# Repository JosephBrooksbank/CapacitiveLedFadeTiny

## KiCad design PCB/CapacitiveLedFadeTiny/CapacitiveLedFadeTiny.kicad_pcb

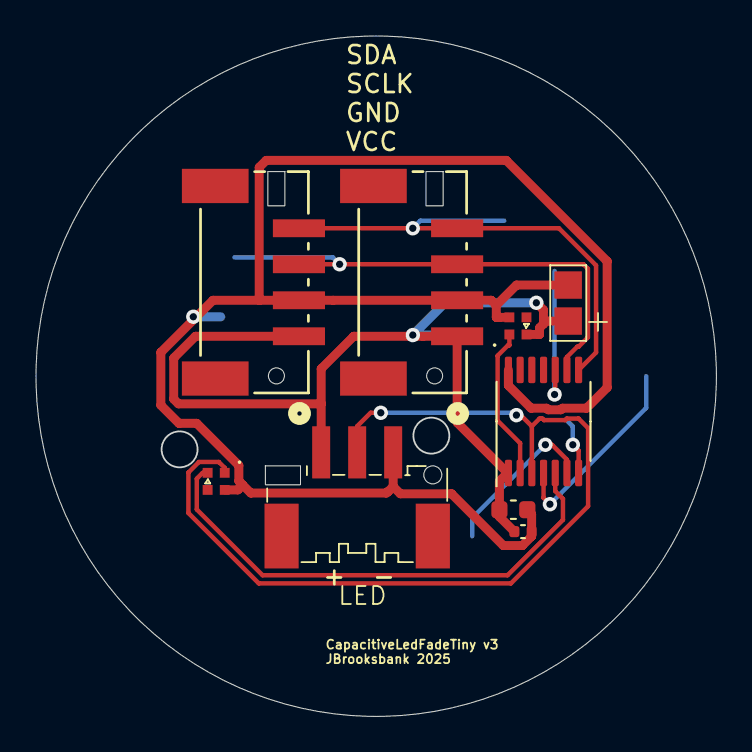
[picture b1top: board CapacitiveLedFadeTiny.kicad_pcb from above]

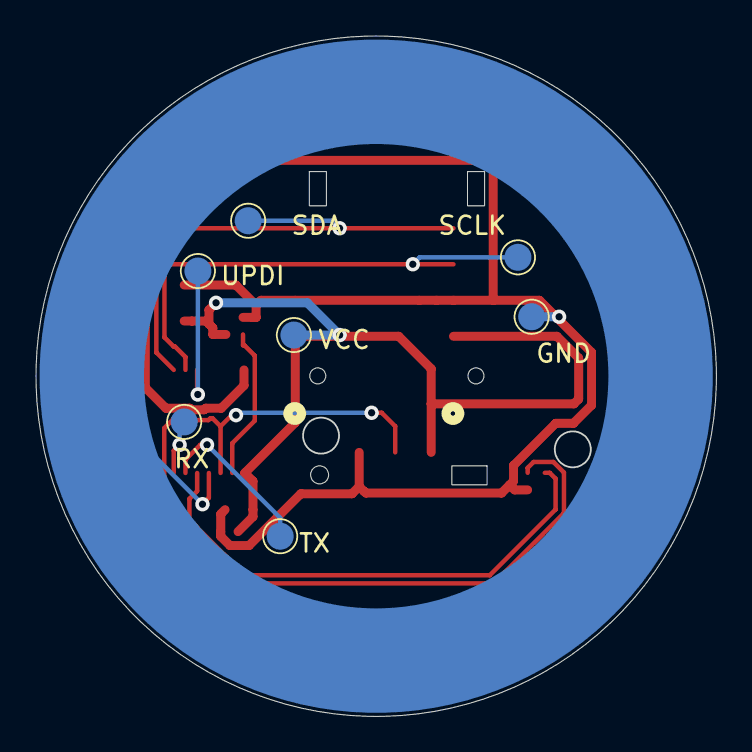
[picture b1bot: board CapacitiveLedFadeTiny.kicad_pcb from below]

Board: 2 copper layers, 37.7 x 37.7 mm, 17 parts (7 on the bottom side), 11 nets.

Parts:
BusIn1: Bus In; CONN_BM04B-PASS-1-TFTLFSN_JST
BusOut1: Bus Out; CONN_BM04B-PASS-1-TFTLFSN_JST
C3: 0.1uf; C_0402_1005Metric
C4: 1uf; C_0603_1608Metric
GND: GND; TestPoint_Pad_1.5mm_circular
J1: Antenna; CapacitiveAntenna
J6: Power Inject; 2Pad
LED: LEDs; BM03B-PASS-1-TFT
LED1, LED2: SK6805-EC15
RX: PadRX; TestPoint_Pad_1.5mm_circular
SCLK: SCLK; TestPoint_Pad_1.5mm_circular
SDA: SDA; TestPoint_Pad_1.5mm_circular
TX: PadTX; TestPoint_Pad_1.5mm_circular
U1: ATtiny3224-X; TSSOP-14_4.4x5mm_P0.65mm
UPDI: PadUPDI; TestPoint_Pad_1.5mm_circular
VCC: VCC; TestPoint_Pad_1.5mm_circular

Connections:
/LED_Signal: LED.2, LED1.1 (DIN), U1.3 (PA5)
/RX: RX.1, U1.7 (PB2)
/SCLK: BusIn1.3, BusOut1.3, SCLK.1, U1.9 (PB0)
/SDA: BusIn1.4, BusOut1.4, SDA.1, U1.8 (PB1)
/TX: TX.1, U1.6 (PB3)
/UPDI: U1.10 (~RESET/PA0), UPDI.1
GND: BusIn1.2, BusOut1.2, C3.2, C4.2, GND.1, J6.2, LED.3, LED1.4 (GND), LED2.4 (GND), U1.14 (GND)
unnamed: J1.1, U1.4 (PA6)
unnamed: LED1.2 (VDD), U1.5 (PA7)
unnamed: LED2.1 (DIN), U1.2 (PA4)
VCC: BusIn1.1, BusOut1.1, C3.1, C4.1, J6.1, LED.1, LED2.2 (VDD), U1.1 (VCC), VCC.1

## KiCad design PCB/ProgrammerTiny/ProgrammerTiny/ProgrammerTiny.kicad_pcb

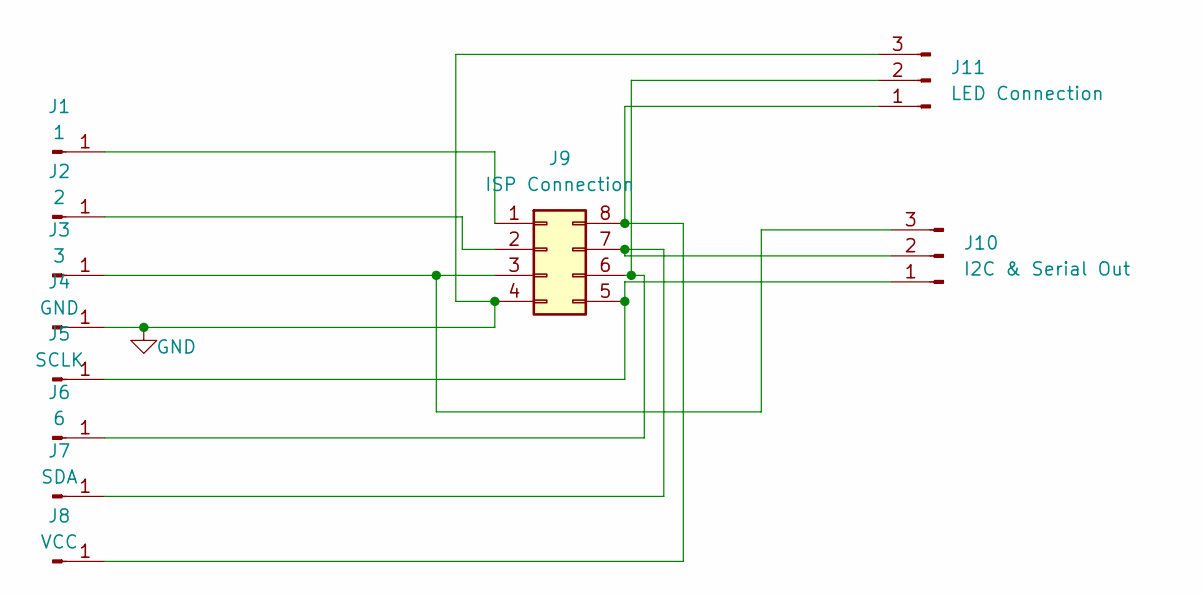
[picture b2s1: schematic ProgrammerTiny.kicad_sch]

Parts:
J1: 1; P75-E2 Through Hole
J2: 2; P75-E2 Through Hole
J3: 3; P75-E2 Through Hole
J4: GND; P75-E2 Through Hole
J5: SCLK; P75-E2 Through Hole
J6: 6; P75-E2 Through Hole
J7: SDA; P75-E2 Through Hole
J8: VCC; P75-E2 Through Hole
J9: ISP Connection; PinHeader_2x04_P2.54mm_Horizontal
J10: I2C & Serial Out; PinHeader_1x03_P2.54mm_Horizontal
J11: LED Connection; PinHeader_1x03_P2.54mm_Horizontal

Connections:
GND: J4.1, J9.4, J11.3
unnamed: J1.1, J9.1
unnamed: J2.1, J9.2
unnamed: J5.1, J9.5, J10.1
unnamed: J7.1, J9.7, J10.2
unnamed: J3.1, J9.3, J10.3
unnamed: J8.1, J9.8, J11.1
unnamed: J6.1, J9.6, J11.2

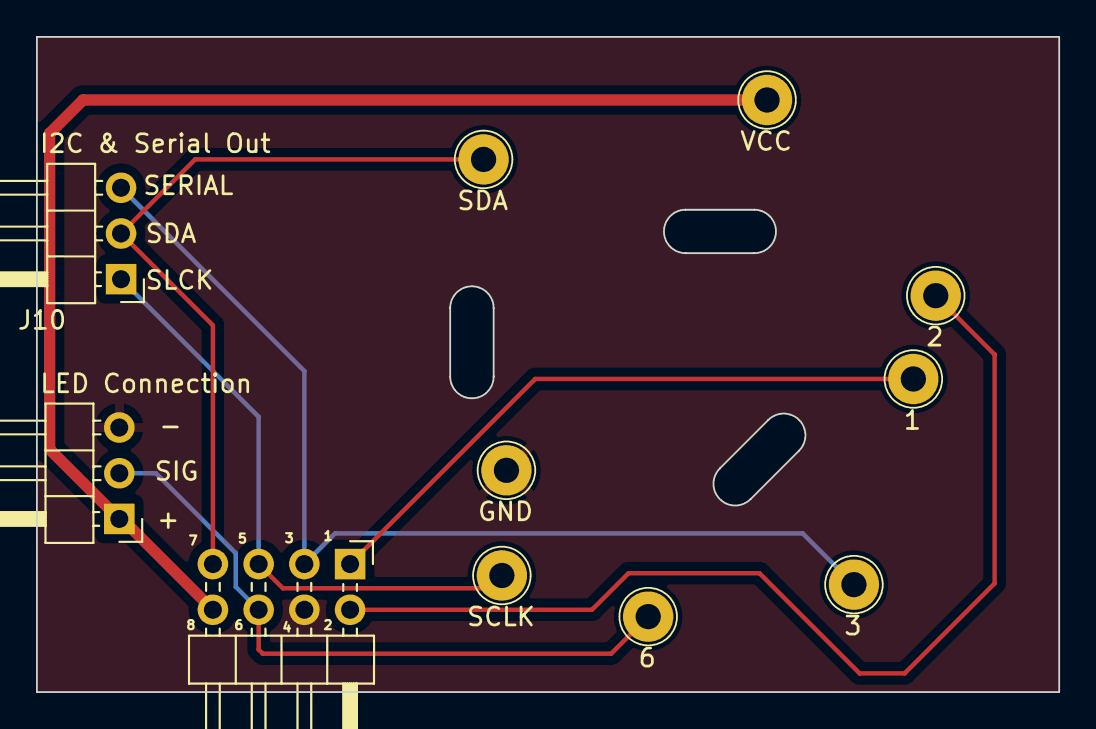
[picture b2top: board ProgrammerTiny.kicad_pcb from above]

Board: 2 copper layers, 56.8 x 36.4 mm, 11 parts (0 on the bottom side), 8 nets.

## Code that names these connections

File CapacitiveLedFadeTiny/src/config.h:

#ifndef CONFIG_H
#define CONFIG_H

#include "Arduino.h"

#define TOUCH_SENSE 5
#define OFF_DELAY 200

#define BAUD_RATE 115200
#define NUM_LEDS 30
#define ENABLE_DEBUG_LED_PIN PIN_PA7
#define STATUS_PIN PIN_PA4
#define SENSE_PIN PIN_PA6
#define LED_DRIVER WS2812
#define LED_PIN PIN_PA5


// i2c stuff
#define USE_I2C
#define I2C_ADDRESS 14


// Software Serial Stuff
#ifndef USE_I2C
    #define USE_SOFTWARE_SERIAL
    #define SOFTWARE_BAUD 9600
    #define RX_PIN PIN_PB0
    #define TX_PIN PIN_PB1
#endif


#define USE_ONBOARD_LED
#define USE_STATUS_LED


#endif

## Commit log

2024-09-12 Initial Commit
    Sets up Tiny (Target) board with LED and Software based serial
    Sets up Arduino Mega (Controller) as serial interpreter
2024-09-13 Add LED control, config file, conditional serial
2024-09-16 idea file changes
    usually I gitignore these but I'm trying to keep them in sync for once
2024-10-05 Create PCB
2024-10-05 Send / Receive i2c main board
2024-10-05 Add 'digispark' style attiny dev board environment
2024-10-05 i2c on peripheral, testing communications
2024-10-06 remove unnecessary .idea items
2024-10-06 Sync all modules to fast rainbow
    This is not very stable with the breadboard and random dev boards I have hooked up right now. I'm hoping that when used with consistent uniform PCBs i2c will fail less
    Also, this is a very inefficient way to handle cycling colors.
    TODO: main board keeps in sync with _occasional_ messages, modules boards handle most of the animation themselves
2024-10-07 Update board layout
    the attiny is actually a wider footprint :kms:
    this is why we do prototype boards
2024-10-08 update config value after flashing some chips
    also remove unused function
2024-10-12 v2 of I2C board
2024-10-12 Add programmer board for v2
2024-10-28 Idea files
    I'm so tired of this shit
2024-10-28 echo i2c info on tinys
2024-10-28 Begin work on arduino controller for i2c testing
2024-11-01 update gitignore
2024-11-01 move led module down one level in repo
2024-11-03 Move some things out to classes, i2c working as echo
2024-11-03 Read led strip status via i2c
2024-11-03 Read LED status via i2c, control board
2024-11-04 Turn other strips on when one is turned on
2024-11-04 Dont delay loop, actually update struct in array
2024-11-04 re-add .idea folder stuff
    platformio isn't working correctly on my laptop so I'll see if this helps
2024-11-05 small updates
2024-11-05 rename files from .h to .hpp
    made me uncomfortable that they could be misunderstood to be c files
2024-11-05 Add 'color' and 'fade' as commands
2024-11-05 send commands to main board via serial
2024-11-06 work more on getting i2c working
    sending the global 'r' command on basically every cycle was _not_ helping and was overwriting other one-off commands like color changes
    I'm not sure if `setWireTimeout` really does much but it doesno seem to hurt
2024-11-06 add more user commands
    some _extremely_ messy code here to try more structures out for sending display commands from the arduino to the led modules. My current goal is a 'splash' pattern out from the point of contact- the 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
    I think to do this in a way that looks nice I won't be able to sequentially tell each cell to start fading on, since there may be upwards of 10 outer cells trying to turn on at the same time. Instead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
    Other thoughts:
    per
2024-11-17 this shit is not working
2024-11-17 send the time that the module has been touched, accurate up to ~8ms
    This should help with synchronizing when other modules should turn on in patterns
    my first direct register use!
2024-11-25 Add config mode, update controller
2024-11-25 begin work on ripple
2024-11-27 continue work on ripple
2024-11-27 remove softwareserial and polymorphism
    don't need it and it added overhead
2024-11-27 Move file level vars into structs for organization
    I hope to eventually move this all into separate files and stuff
2024-11-27 begin work on Command struct
    rather than use (expensive) polymorphism, really all we need for the Command type is an idenfitier and a function to run, theoretically.
    There might be more necessary as there is state to change.
    TODO: make all of the `Mode`s into enums, pack into single byte if possible.
    TODO: take another shot at moving some of the FastLED stuff to another file. Don't get fancy with it, just a header file so that things like `turnOn` can be referenced from other files
2024-12-03 wip on ripple
2024-12-07 begin work on refactor
    I figured out how to get FastLED to work in other files. Taking another shot at splitting out the code into their own classes, because the original main was impossible to work with after not touching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
2024-12-08 Add LedBehavior controller, animation modes, send context over i2c
2024-12-10 add AddressMap to track status of other modules
2024-12-10 Add Commands for setting mode and setting other device state
2024-12-10 alternate mode command parsing
2024-12-10 remove unused reference
2024-12-12 TimingGroup for animations!
2024-12-15 Begin work to allow timing groups set over i2c
2024-12-15 Add method to create addressmap from buffer
2024-12-16 wip lower ram usage
2024-12-16 minor improvements to stack memory while getting timinggroup from i2c
2024-12-16 Start work with EEPROM
    going to move all config values to EEPROM. They shouldn't be changing very often, this way the changes will persist across reboots, and we'll be able to have a bunch more timing groups without worryi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
2024-12-17 begin moving config values to eeprom
    these values _can_ change, but likely won't change very often. So can't be flash, but we can save RAM by moving them to EEPROM
2025-02-19 v3 pcb
2025-02-19 pcb v3.1
2025-02-20 v3.2 pcb, changed to PA connectors
2025-03-13 v3 pcb again?
2025-03-13 v3 code begins
    cleaned up most of it, really don't need a lot of it for the final goal. Todo still:
    - store config values in EEPROM
    - i2c to set config values
    - alternate color mode (whole board one color)
2025-03-13 Wire working
    also optional software serial as a backup
2025-03-13 add windows env, dont track vscode folder
2025-03-16 store variable config values in EEPROM, accept over i2c
    so much easier than expected lol
2025-03-17 Add workspace with shared folder
2025-03-17 Add mode for consistent single color
2025-03-17 set scl manually
    the default wire frequency setting method does not make use of the prescaler, so extremely slow speeds are not available
2025-03-17 capture various i2c speed data
2025-03-17 wip: fade off animation timer
2025-03-17 fade out LEDs, don't fade status led
2025-03-18 Add rainbow animation mode
2025-03-18 change version to a 'should_save' variable to make writes to eeprom more intentional
    also did some timing study to clock in (this current board) to a steady 60 fps animation timing. Some investigation will need to be done with other boards to see how consistent that is- maybe we'll n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
    with 'synced rainbow' mode, the config data is being sent many times per second. If this was written to eeprom every time we would wear it down quite quickly.
    sending the entire config object just to update the hue is quite inefficient, but since we're animating at 60fps we can afford to be slo
2025-07-15 push before reformat
2026-04-28 Add port for mac upload
